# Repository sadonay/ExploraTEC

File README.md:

# ExploraTEC
Proyectos del Area de Exploración Tecnológica de la Universidad del Desarrollo, Concepción

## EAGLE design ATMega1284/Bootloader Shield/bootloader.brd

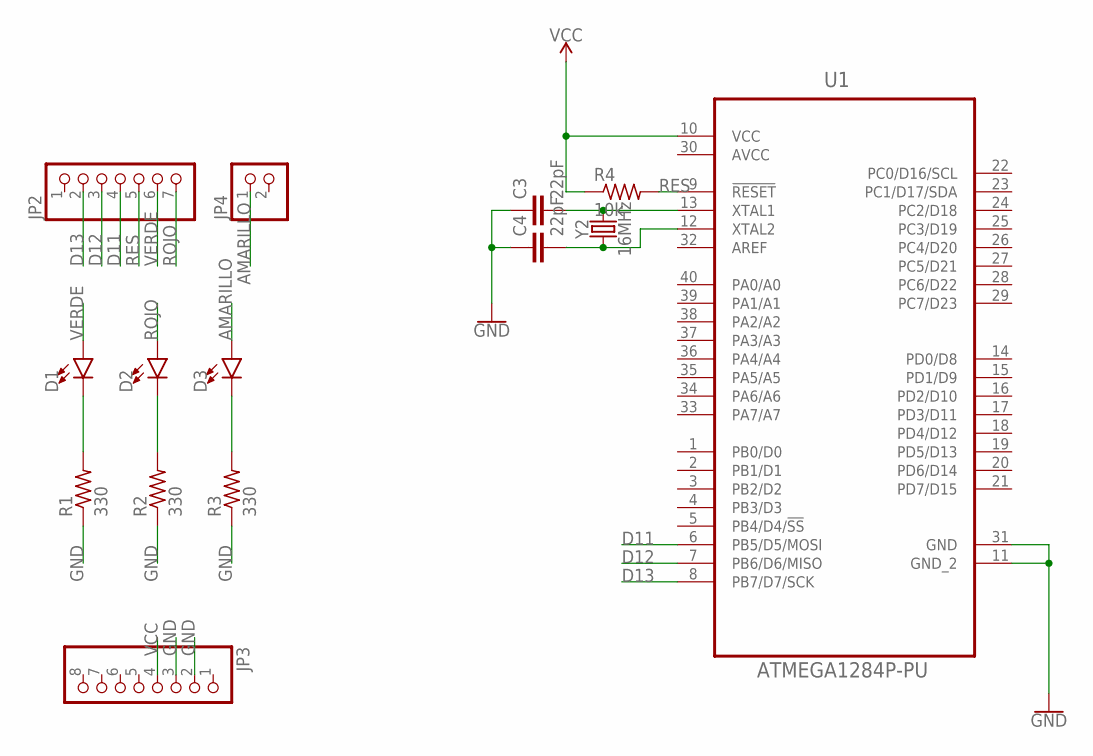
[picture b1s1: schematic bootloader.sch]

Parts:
C3, C4: 22pF; C1206
D1, D2, D3: LED1206; LED-1206
JP2: PINHD-1X7; 1X07
JP3: PINHD-1X8; 1X08
JP4: PINHD-1X2; 1X02
R1, R2, R3: 330; R1206
R4: 10k; R1206
U1: ATMEGA1284P-PU; DIP254P1524X483-40
Y2: 16MHz; CRYSTAL-SMD-5X3.2-4PAD

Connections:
AMARILLO: D3.A, JP4.1
AVCC: U1.30 (AVCC)
D11: JP2.4, U1.6 (PB5/D5/MOSI)
D12: JP2.3, U1.7 (PB6/D6/MISO)
D13: JP2.2, U1.8 (PB7/D7/SCK)
GND: C3.1, C4.1, JP3.2, JP3.3, R1.1, R2.1, R3.1, U1.11 (GND_2), U1.31 (GND)
unnamed: D1.C, R1.2
unnamed: D2.C, R2.2
unnamed: D3.C, R3.2
unnamed: C4.2, U1.12 (XTAL2), Y2.1
unnamed: C3.2, U1.13 (XTAL1), Y2.3 (2)
RES: JP2.5, R4.2, U1.9 (!RESET)
ROJO: D2.A, JP2.7
VCC: JP3.4, R4.1, U1.10 (VCC)
VERDE: D1.A, JP2.6

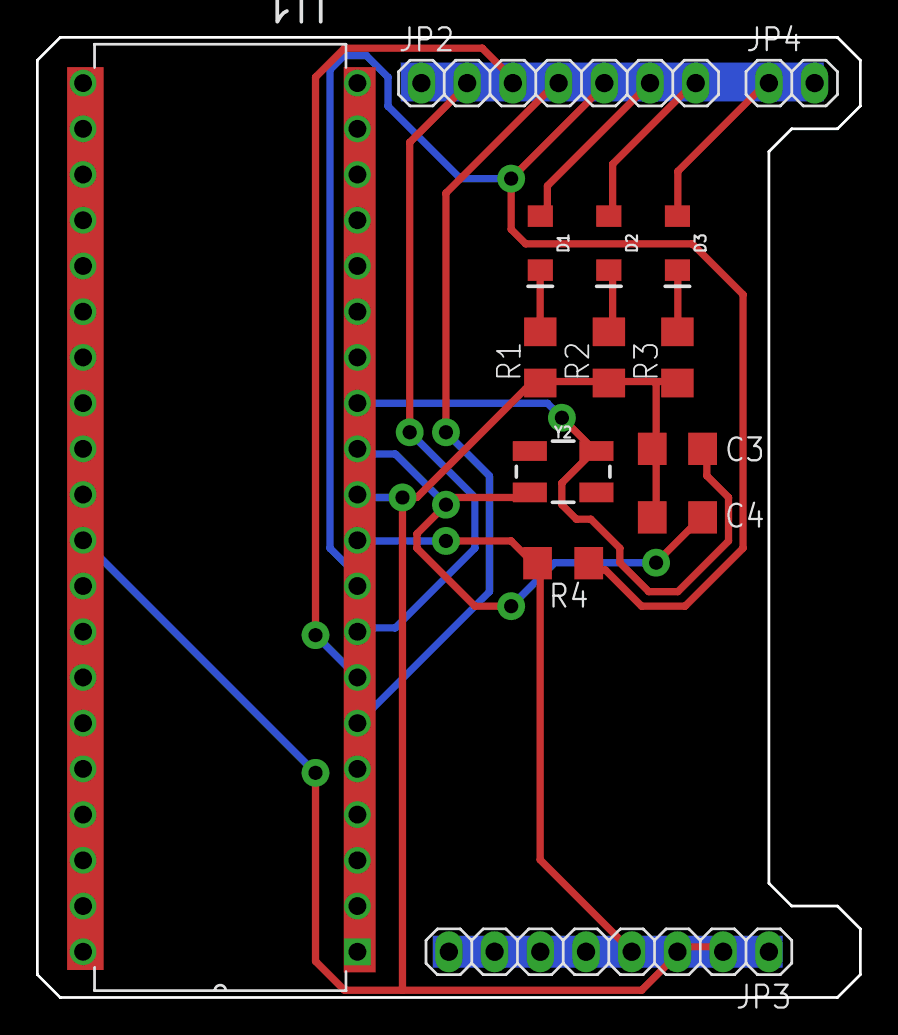
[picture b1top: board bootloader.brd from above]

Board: 2 copper layers, 45.7 x 53.3 mm, 14 parts (0 on the bottom side), 14 nets.

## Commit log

2019-12-01 Rename bootloader.brd to ATMega1284/Bootloader Shield/bootloader.brd
2019-12-01 Rename bootloader.sch to ATMega1284/Bootloader Shield/bootloader.sch

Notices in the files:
parts and their libraries:
SparkFun-LED: Licensing: Creative Commons ShareAlike 4.0 International - https://creativecommons.org/licenses/by-sa/4.0
